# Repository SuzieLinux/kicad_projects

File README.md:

This repository has misc kicad projects
If you feel that it is worth something for you you can go to my website and make a donation using the donate button which brings you to paypal
https://suzielinux.com/

The project lcd_adapter is a board to adapt the 3.2 or 3.4 inch LCD designed
for the RPI so they can be used with other boards like my RL78 boards or
Linux boards like the beagle boards, youyeetoo, cubitruck, odroid or others.

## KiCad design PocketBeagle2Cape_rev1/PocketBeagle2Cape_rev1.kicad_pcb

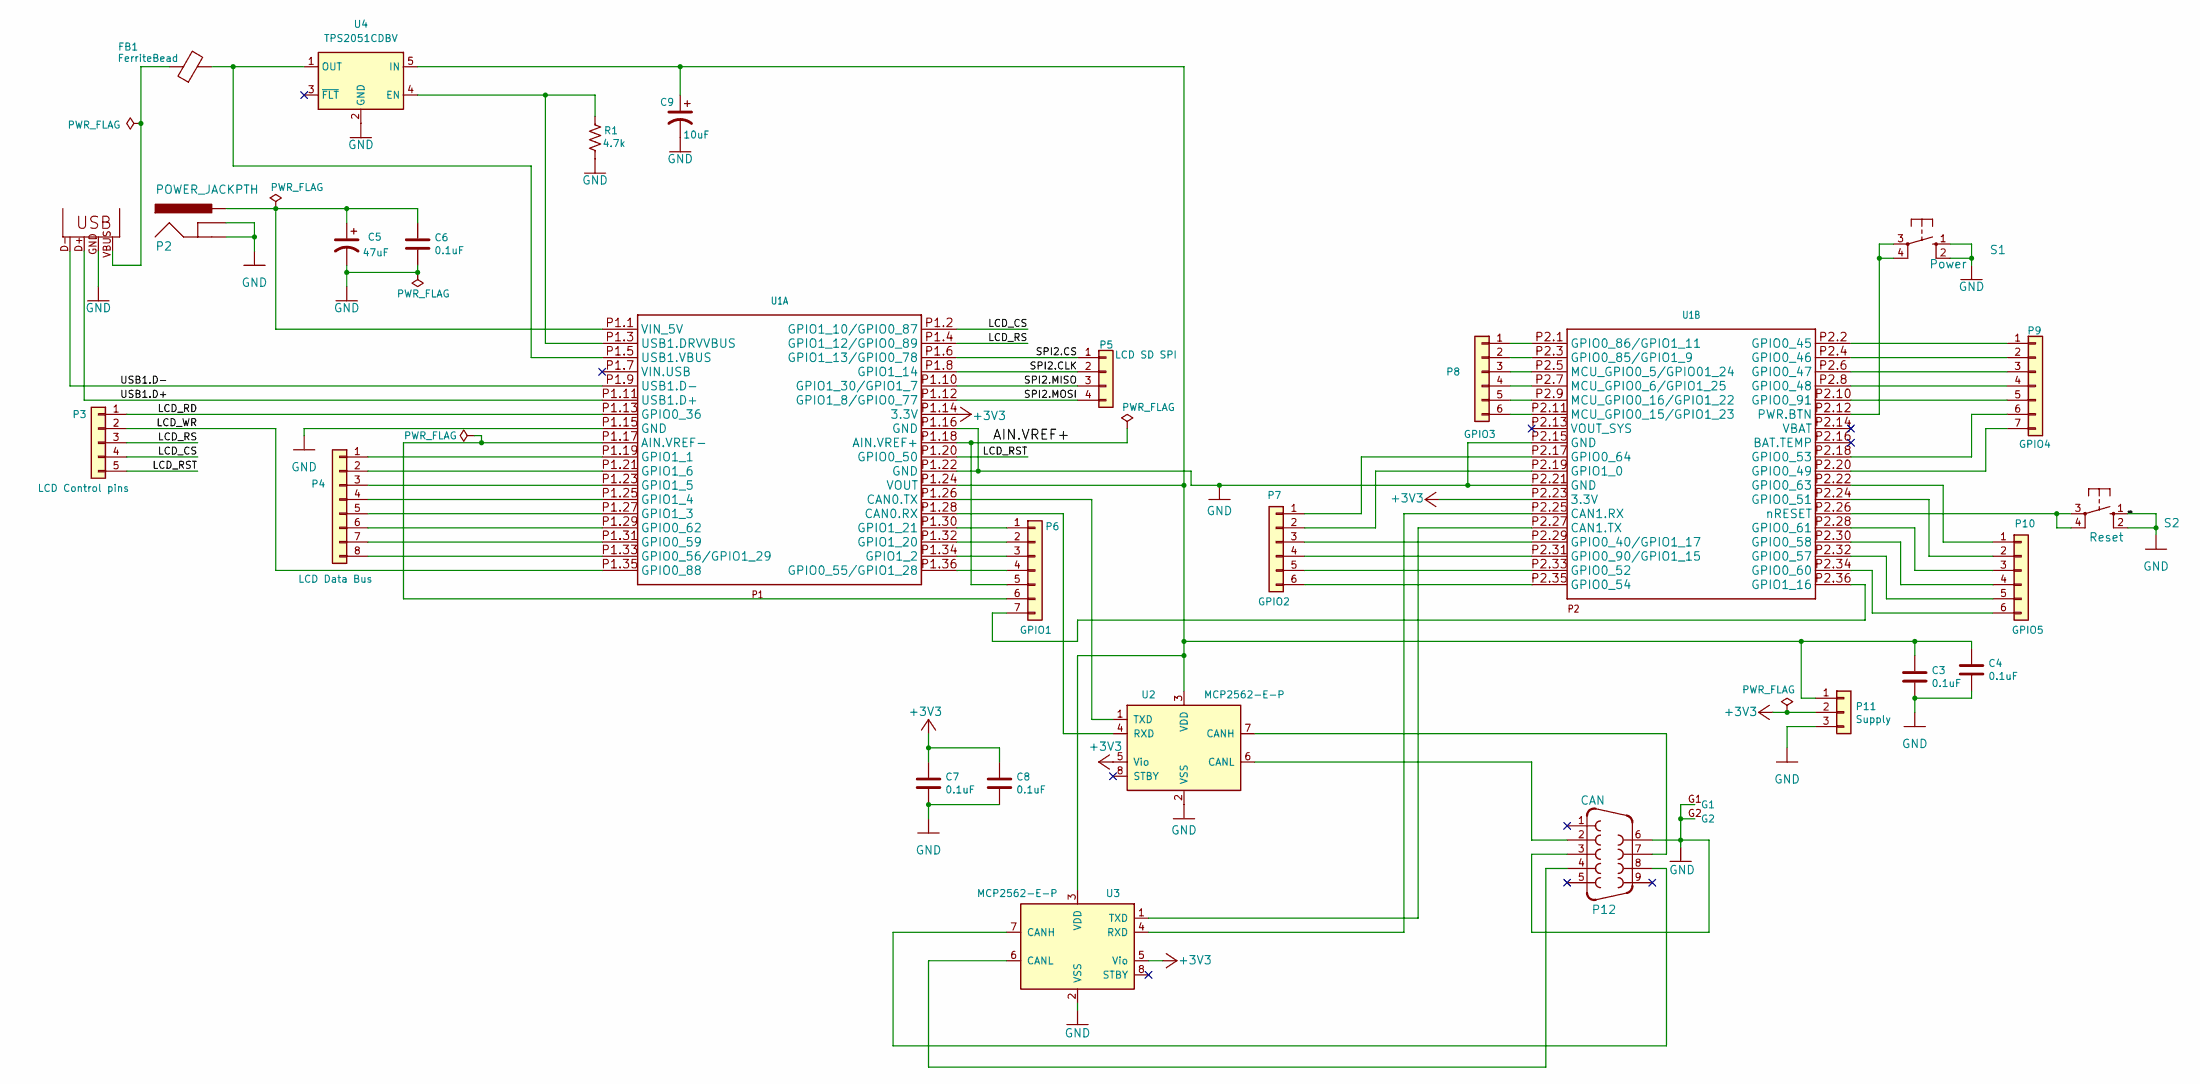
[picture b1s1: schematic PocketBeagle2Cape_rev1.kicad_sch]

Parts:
C3, C4, C6, C7, C8: 0.1uF; C_0805_2012Metric
C5: 47uF; CP_Radial_D6.3mm_P2.50mm
C9: 10uF; CP_Radial_D5.0mm_P2.50mm
FB1: FerriteBead; D_0805_2012Metric
P1: USB-A-H
P2: POWER_JACKPTH; POWER_JACK_PTH
P3: LCD Control pins; PinHeader_1x05_P2.00mm_Vertical
P4: LCD Data Bus; PinHeader_1x08_P2.00mm_Vertical
P5: LCD SD SPI; PinHeader_1x04_P2.00mm_Vertical
P6: GPIO1; PinHeader_1x07_P2.00mm_Vertical
P7: GPIO2; PinHeader_1x06_P2.00mm_Vertical
P8: GPIO3; PinHeader_1x06_P2.00mm_Vertical
P9: GPIO4; PinHeader_1x07_P2.00mm_Vertical
P10: GPIO5; PinHeader_1x06_P2.00mm_Vertical
P11: Supply; PinSocket_1x03_P2.54mm_Vertical
P12: CAN; F09HP
R1: 4.7k; R_0805_2012Metric
S1: Power; B3F-10XX
S2: Reset; B3F-10XX
U1: PocketBeagle2
U2, U3: MCP2562-E-P; SO-8_3.9x4.9mm_P1.27mm
U4: TPS2051CDBV; SOT-23-5

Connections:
+3V3: C7.1, C8.1, P11.2, U1.P1.14 (3.3V), U1.P2.23 (3.3V), U2.5 (Vio), U3.5 (Vio)
/AIN.VREF+: P6.5, U1.P1.18 (AIN.VREF+)
/LCD_CS: P3.4, U1.P1.2 (GPIO1_10/GPIO0_87)
/LCD_RD: P3.1, U1.P1.13 (GPIO0_36)
/LCD_RS: P3.3, U1.P1.4 (GPIO1_12/GPIO0_89)
/LCD_RST: P3.5, U1.P1.20 (GPIO0_50)
/LCD_WR: P3.2, U1.P1.35 (GPIO0_88)
/SPI2.CLK: P5.2, U1.P1.8 (GPIO1_14)
/SPI2.CS: P5.1, U1.P1.6 (GPIO1_13/GPIO0_78)
/SPI2.MISO: P5.3, U1.P1.10 (GPIO1_30/GPIO1_7)
/SPI2.MOSI: P5.4, U1.P1.12 (GPIO1_8/GPIO0_77)
/USB1.D+: P1.D+ (D-), U1.P1.11 (USB1.D+)
/USB1.D-: P1.D- (D+), U1.P1.9 (USB1.D-)
GND: C3.2, C4.2, C5.2, C6.2, C7.2, C8.2, C9.2, P1.GND (VBUS), P2.GND, P2.GNDBREAK, P11.3, P12.3, P12.6, P12.G1, P12.G2, R1.2, S1.1 (S), S1.2 (S1), S2.1 (S), S2.2 (S1), U1.P1.15 (GND), U1.P1.16 (GND), U1.P1.22 (GND), U1.P2.15 (GND), U1.P2.21 (GND), U2.2 (VSS), U3.2 (VSS), U4.2 (GND)
unnamed: FB1.1, P1.VBUS (GND)
unnamed: P4.1, U1.P1.19 (GPIO1_1)
unnamed: P4.2, U1.P1.21 (GPIO1_6)
unnamed: P4.3, U1.P1.23 (GPIO1_5)
unnamed: P4.4, U1.P1.25 (GPIO1_4)
unnamed: P4.5, U1.P1.27 (GPIO1_3)
unnamed: P4.6, U1.P1.29 (GPIO0_62)
unnamed: P4.7, U1.P1.31 (GPIO0_59)
unnamed: P4.8, U1.P1.33 (GPIO0_56/GPIO1_29)
unnamed: P6.1, U1.P1.30 (GPIO1_21)
unnamed: P6.2, U1.P1.32 (GPIO1_20)
unnamed: P6.3, U1.P1.34 (GPIO1_2)
unnamed: P6.4, U1.P1.36 (GPIO0_55/GPIO1_28)
unnamed: P6.6, U1.P1.17 (AIN.VREF-)
unnamed: P6.7, U1.P2.36 (GPIO1_16)
unnamed: P7.1, U1.P2.17 (GPIO0_64)
unnamed: P7.2, U1.P2.19 (GPIO1_0)
unnamed: P7.3, U1.P2.29 (GPIO0_40/GPIO1_17)
unnamed: P7.4, U1.P2.31 (GPIO0_90/GPIO1_15)
unnamed: P7.5, U1.P2.33 (GPIO0_52)
unnamed: P7.6, U1.P2.35 (GPIO0_54)
unnamed: P8.1, U1.P2.1 (GPIO0_86/GPIO1_11)
unnamed: P8.2, U1.P2.3 (GPIO0_85/GPIO1_9)
unnamed: P8.3, U1.P2.5 (MCU_GPIO0_5/GPIO01_24)
unnamed: P8.4, U1.P2.7 (MCU_GPIO0_6/GPIO1_25)
unnamed: P8.5, U1.P2.9 (MCU_GPIO0_16/GPIO1_22)
unnamed: P8.6, U1.P2.11 (MCU_GPIO0_15/GPIO1_23)
unnamed: P9.1, U1.P2.2 (GPIO0_45)
unnamed: P9.2, U1.P2.4 (GPIO0_46)
unnamed: P9.3, U1.P2.6 (GPIO0_47)
unnamed: P9.4, U1.P2.8 (GPIO0_48)
unnamed: P9.5, U1.P2.10 (GPIO0_91)
unnamed: P9.6, U1.P2.18 (GPIO0_53)
unnamed: P9.7, U1.P2.20 (GPIO0_49)
unnamed: P10.1, U1.P2.22 (GPIO0_63)
unnamed: P10.2, U1.P2.24 (GPIO0_51)
unnamed: P10.3, U1.P2.28 (GPIO0_61)
unnamed: P10.4, U1.P2.30 (GPIO0_58)
unnamed: P10.5, U1.P2.32 (GPIO0_57)
unnamed: P10.6, U1.P2.34 (GPIO0_60)
unnamed: C3.1, C4.1, C9.1, P11.1, U1.P1.24 (VOUT), U2.3 (VDD), U3.3 (VDD), U4.5 (IN)
unnamed: S1.3, S1.4 (P1), U1.P2.12 (PWR.BTN)
unnamed: S2.3, S2.4 (P1), U1.P2.26 (nRESET)
unnamed: U1.P1.28 (CAN0.RX), U2.4 (RXD)
unnamed: U1.P1.26 (CAN0.TX), U2.1 (TXD)
unnamed: R1.1, U1.P1.3 (USB1.DRVVBUS), U4.4 (EN)
unnamed: FB1.2, U1.P1.5 (USB1.VBUS), U4.1 (OUT)
unnamed: C5.1, C6.1, P2.PWR, U1.P1.1 (VIN_5V)
unnamed: U1.P2.25 (CAN1.RX), U3.4 (RXD)
unnamed: U1.P2.27 (CAN1.TX), U3.1 (TXD)
unnamed: P12.7, U2.7 (CANH)
unnamed: P12.2, U2.6 (CANL)
unnamed: P12.8, U3.7 (CANH)
unnamed: P12.4, U3.6 (CANL)

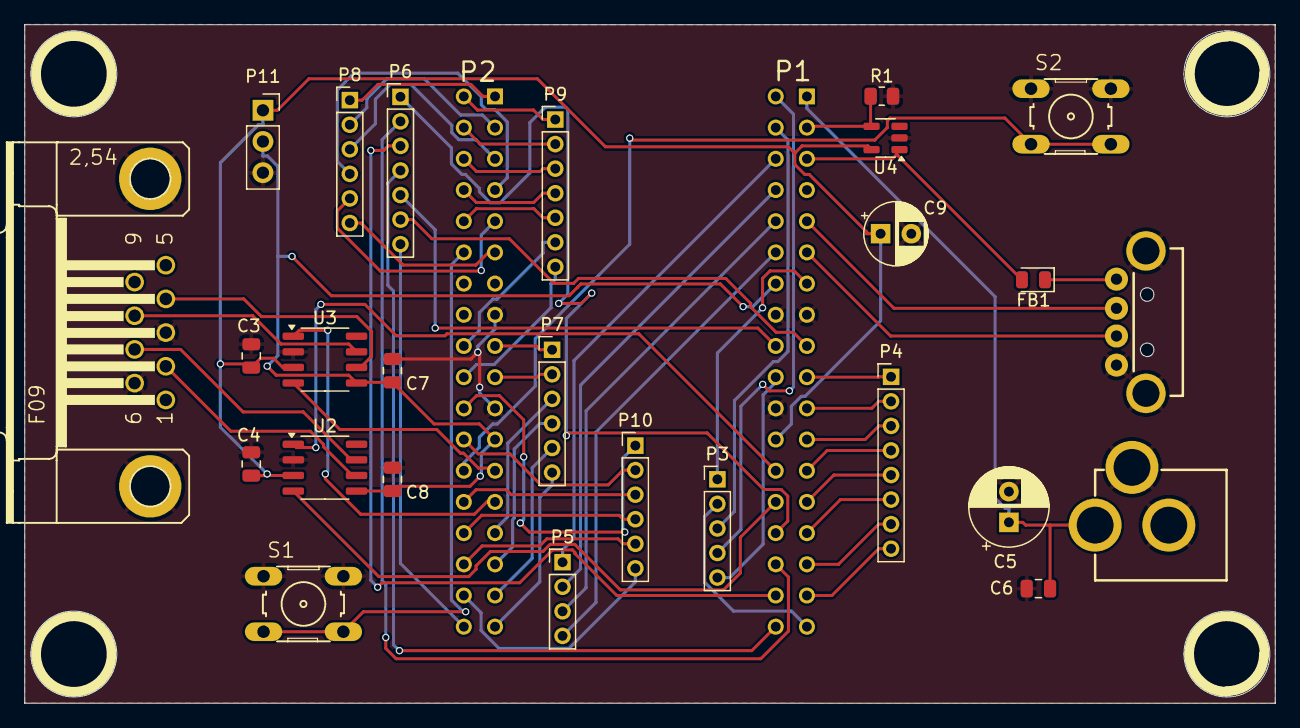
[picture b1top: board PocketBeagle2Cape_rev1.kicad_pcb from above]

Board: 2 copper layers, 101.8 x 55.2 mm, 27 parts (1 on the bottom side), 68 nets.

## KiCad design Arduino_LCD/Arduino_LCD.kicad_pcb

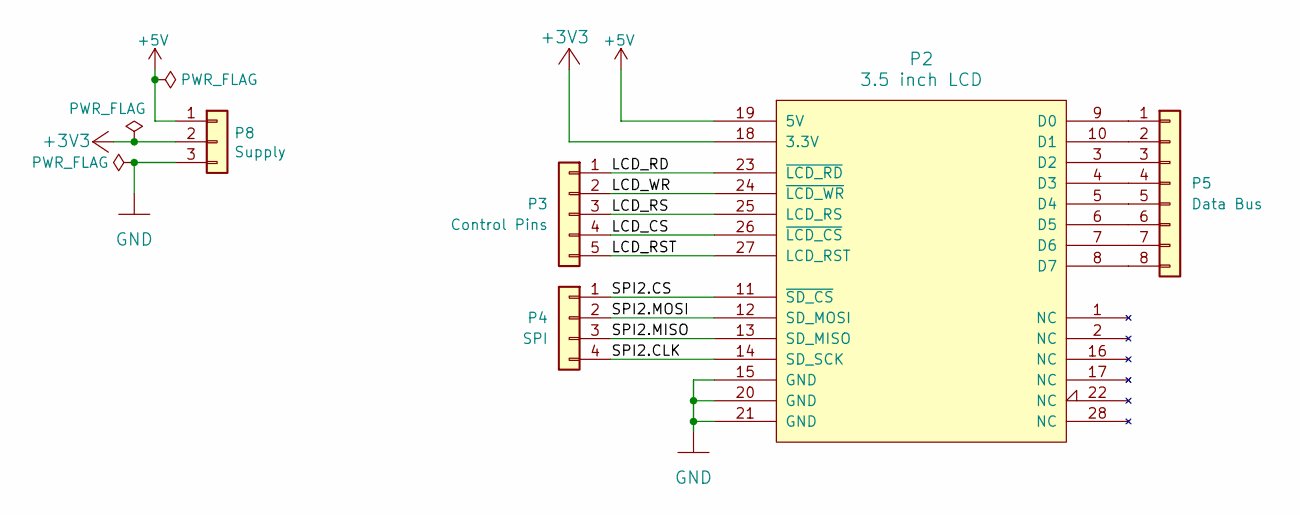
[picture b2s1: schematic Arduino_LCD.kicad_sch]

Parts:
P2: 3.5 inch LCD; ArduinoConnector
P3: Control Pins; PinHeader_1x05_P2.00mm_Vertical
P4: SPI; PinHeader_1x04_P2.00mm_Vertical
P5: Data Bus; PinHeader_1x08_P2.00mm_Vertical
P8: Supply; PinSocket_1x03_P2.54mm_Vertical

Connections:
+3V3: P2.18 (3.3V), P8.2
+5V: P2.19 (5V), P8.1
/LCD_CS: P2.26 (~LCD_CS), P3.4
/LCD_RD: P2.23 (~LCD_RD), P3.1
/LCD_RS: P2.25 (LCD_RS), P3.3
/LCD_RST: P2.27 (LCD_RST), P3.5
/LCD_WR: P2.24 (~LCD_WR), P3.2
/SPI2.CLK: P2.14 (SD_SCK), P4.4
/SPI2.CS: P2.11 (~SD_CS), P4.1
/SPI2.MISO: P2.13 (SD_MISO), P4.3
/SPI2.MOSI: P2.12 (SD_MOSI), P4.2
GND: P2.15 (GND), P2.20 (GND), P2.21 (GND), P8.3
unnamed: P2.9 (D0), P5.1
unnamed: P2.10 (D1), P5.2
unnamed: P2.3 (D2), P5.3
unnamed: P2.4 (D3), P5.4
unnamed: P2.5 (D4), P5.5
unnamed: P2.6 (D5), P5.6
unnamed: P2.7 (D6), P5.7
unnamed: P2.8 (D7), P5.8

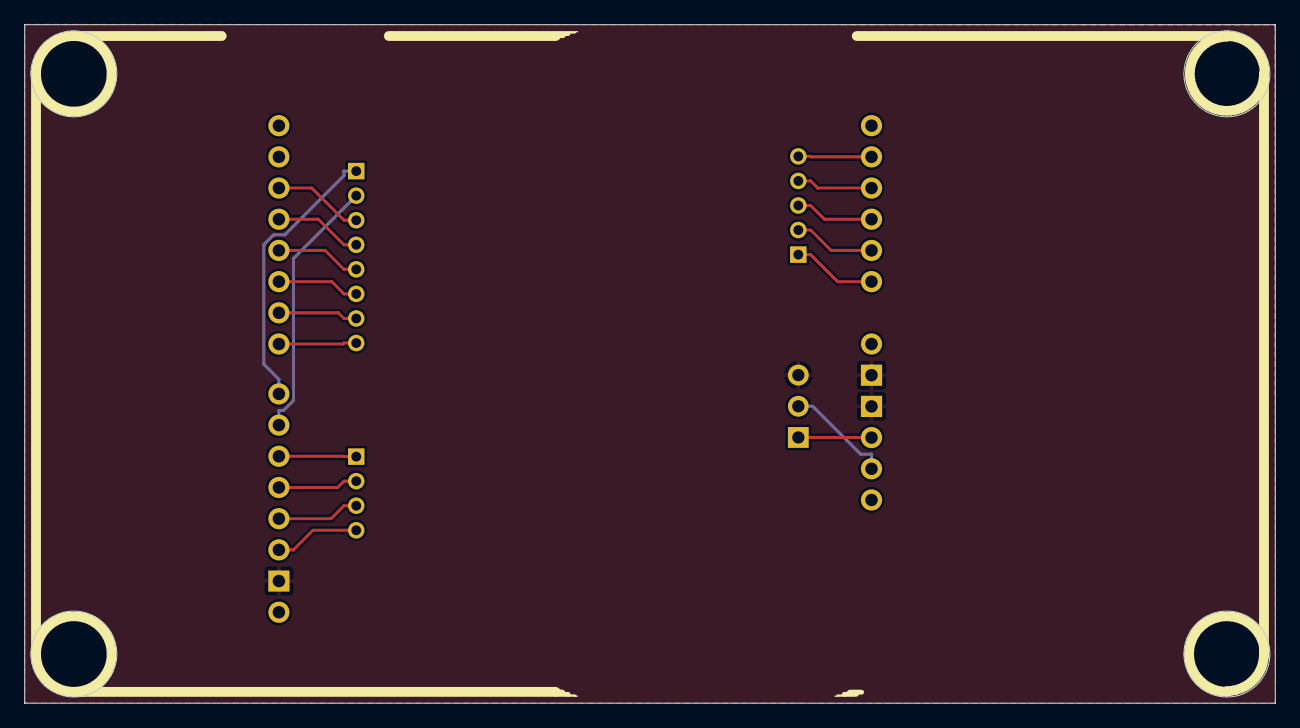
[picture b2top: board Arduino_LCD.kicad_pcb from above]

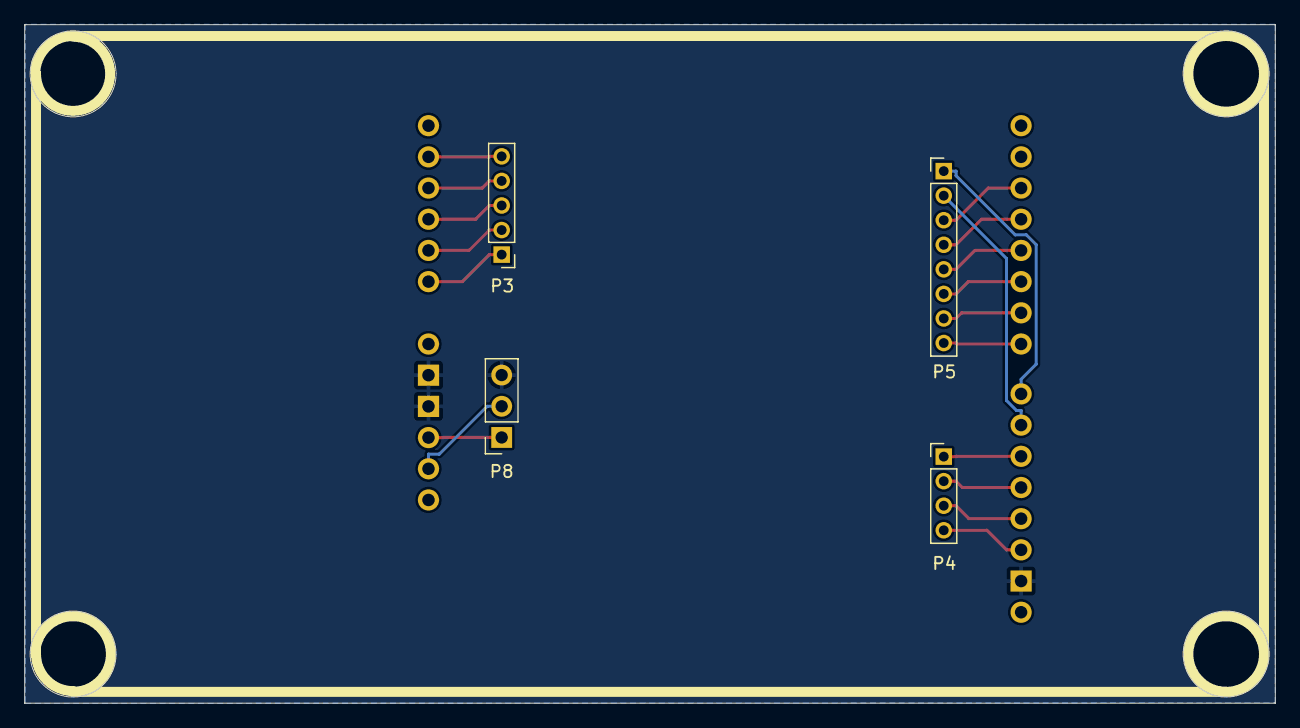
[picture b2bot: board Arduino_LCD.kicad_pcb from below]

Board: 2 copper layers, 101.8 x 55.2 mm, 5 parts (4 on the bottom side), 20 nets.

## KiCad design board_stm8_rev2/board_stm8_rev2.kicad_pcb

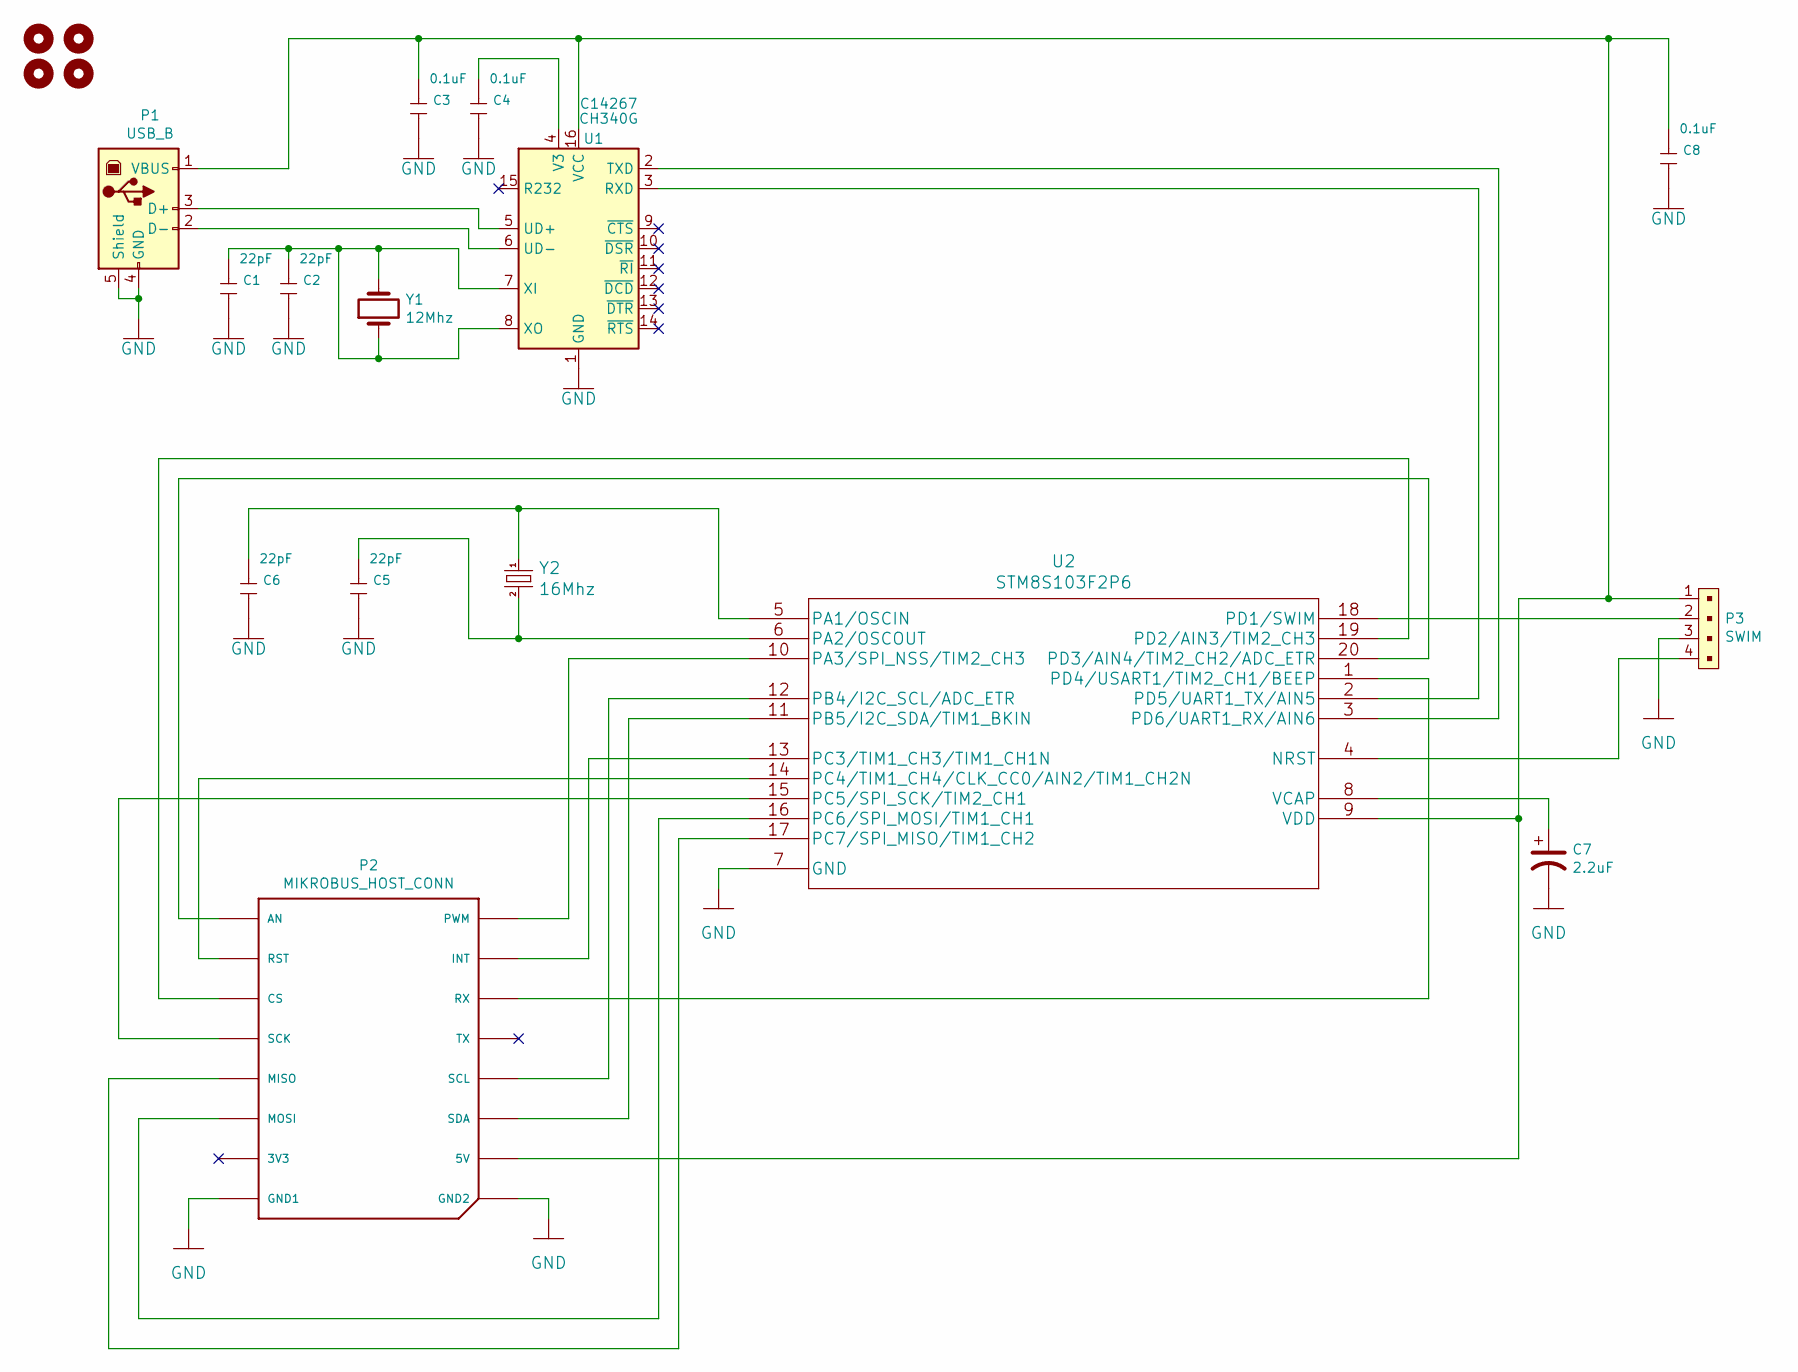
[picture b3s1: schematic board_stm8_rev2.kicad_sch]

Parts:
C1, C2, C5, C6: 22pF; C_0805_2012Metric_Pad1.18x1.45mm_HandSolder; MPN CC0603KRX7R9BB104; LCSC C1562
C3, C4, C8: 0.1uF; C_0805_2012Metric_Pad1.18x1.45mm_HandSolder; MPN CC0603KRX7R9BB104; LCSC C14663
C7: 2.2uF; C_Radial_D5.0mm_H5.0mm_P2.00mm
H1, H2, H3, H4: MountingHole; MountingHole_2.7mm_M2.5_DIN965_Pad
P1: USB_B; USB_B_Lumberg_2411_02_Horizontal
P2: MIKROBUS_HOST_CONN
P3: SWIM; PinHeader_1x4_P2.54mm_Drill1.02mm; MPN 0022232041; Digi-Key_PN WM4202-ND
U1: CH340G; SOIC-16_3.9x9.9mm_P1.27mm; LCSC C14267
U2: STM8S103F2P6
Y1: 12Mhz; Crystal_HC49-4H_Vertical
Y2: 16Mhz; Crystal_HC49-4H_Vertical

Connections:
GND: C1.2, C2.2, C3.2, C4.2, C5.2, C6.2, C7.2, C8.2, P1.4 (GND), P1.5 (Shield), P2.P8 (GND1), P2.P9 (GND2), P3.3, U1.1 (GND), U2.7 (GND)
unnamed: P1.3 (D+), U1.5 (UD+)
unnamed: P1.2 (D-), U1.6 (UD-)
unnamed: C3.1, C8.1, P1.1 (VBUS), P2.P10 (5V), P3.1, U1.16 (VCC), U2.9 (VDD)
unnamed: P2.P1 (AN), U2.20 (PD3/AIN4/TIM2_CH2/ADC_ETR)
unnamed: P2.P3 (CS), U2.19 (PD2/AIN3/TIM2_CH3)
unnamed: P2.P15 (INT), U2.13 (PC3/TIM1_CH3/TIM1_CH1N)
unnamed: P2.P5 (MISO), U2.17 (PC7/SPI_MISO/TIM1_CH2)
unnamed: P2.P6 (MOSI), U2.16 (PC6/SPI_MOSI/TIM1_CH1)
unnamed: P2.P16 (PWM), U2.10 (PA3/SPI_NSS/TIM2_CH3)
unnamed: P2.P2 (RST), U2.14 (PC4/TIM1_CH4/CLK_CC0/AIN2/TIM1_CH2N)
unnamed: P2.P14 (RX), U2.1 (PD4/USART1/TIM2_CH1/BEEP)
unnamed: P2.P4 (SCK), U2.15 (PC5/SPI_SCK/TIM2_CH1)
unnamed: P2.P12 (SCL), U2.12 (PB4/I2C_SCL/ADC_ETR)
unnamed: P2.P11 (SDA), U2.11 (PB5/I2C_SDA/TIM1_BKIN)
unnamed: U1.3 (RXD), U2.2 (PD5/UART1_TX/AIN5)
unnamed: U1.2 (TXD), U2.3 (PD6/UART1_RX/AIN6)
unnamed: C4.1, U1.4 (V3)
unnamed: C1.1, C2.1, U1.7 (XI), U1.8 (XO), Y1.1, Y1.2
unnamed: P3.4, U2.4 (NRST)
unnamed: C6.1, U2.5 (PA1/OSCIN), Y2.1
unnamed: C5.1, U2.6 (PA2/OSCOUT), Y2.2
unnamed: P3.2, U2.18 (PD1/SWIM)
unnamed: C7.1, U2.8 (VCAP)

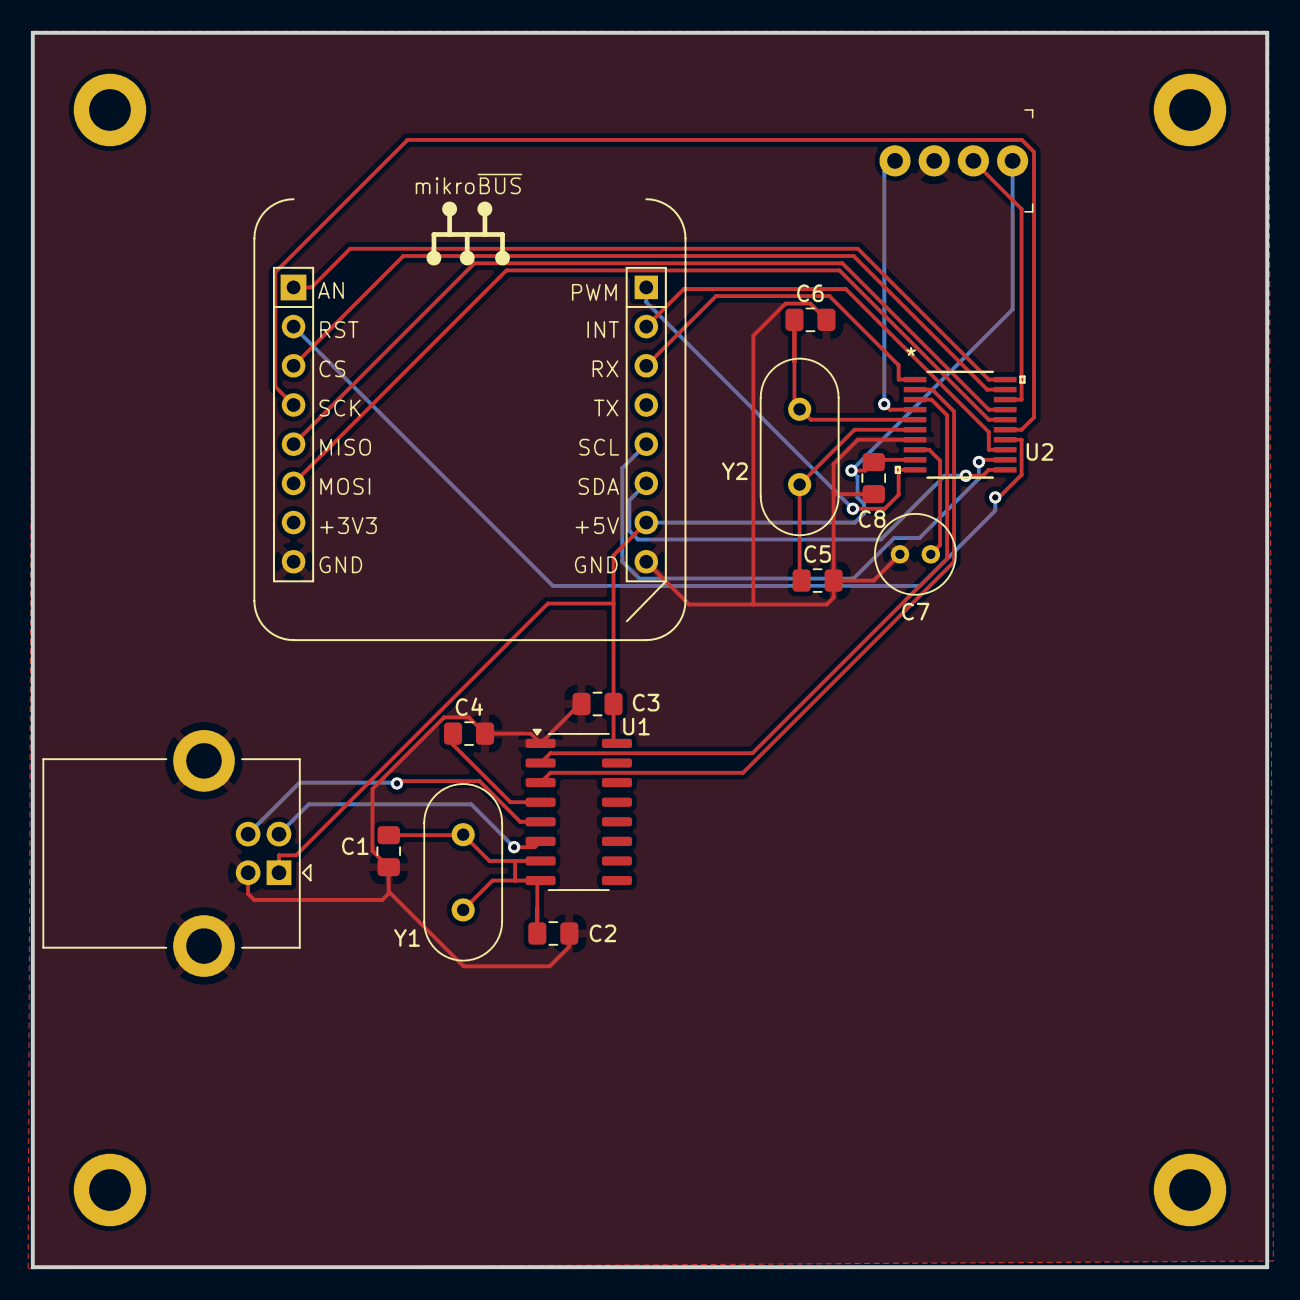
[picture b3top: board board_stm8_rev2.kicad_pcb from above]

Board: 2 copper layers, 80.0 x 80.0 mm, 19 parts (0 on the bottom side), 24 nets.

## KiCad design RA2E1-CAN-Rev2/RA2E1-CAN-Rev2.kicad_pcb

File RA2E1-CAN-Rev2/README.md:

This board uses Renesas R7FA2E1A93 Arm Cortex-M23 device

This is work in progress. I need to test with the evaluation board before I
finalize the design and order boards.

The LCD is Chanruida 1.8 inch TFT LCD 128 × 160 color screen 
ST7735 SPI display LCD module with SD card slot arduino display display lcd

The ethernet adapter is a small board called W5500 SPI to LAN ethernet
network module

It uses a MC2518FD CAN FD device

The debugger used is E2 Lite.

Feel free to use this board but if you are going to make money with it be
nice enough to make a donation on my website.

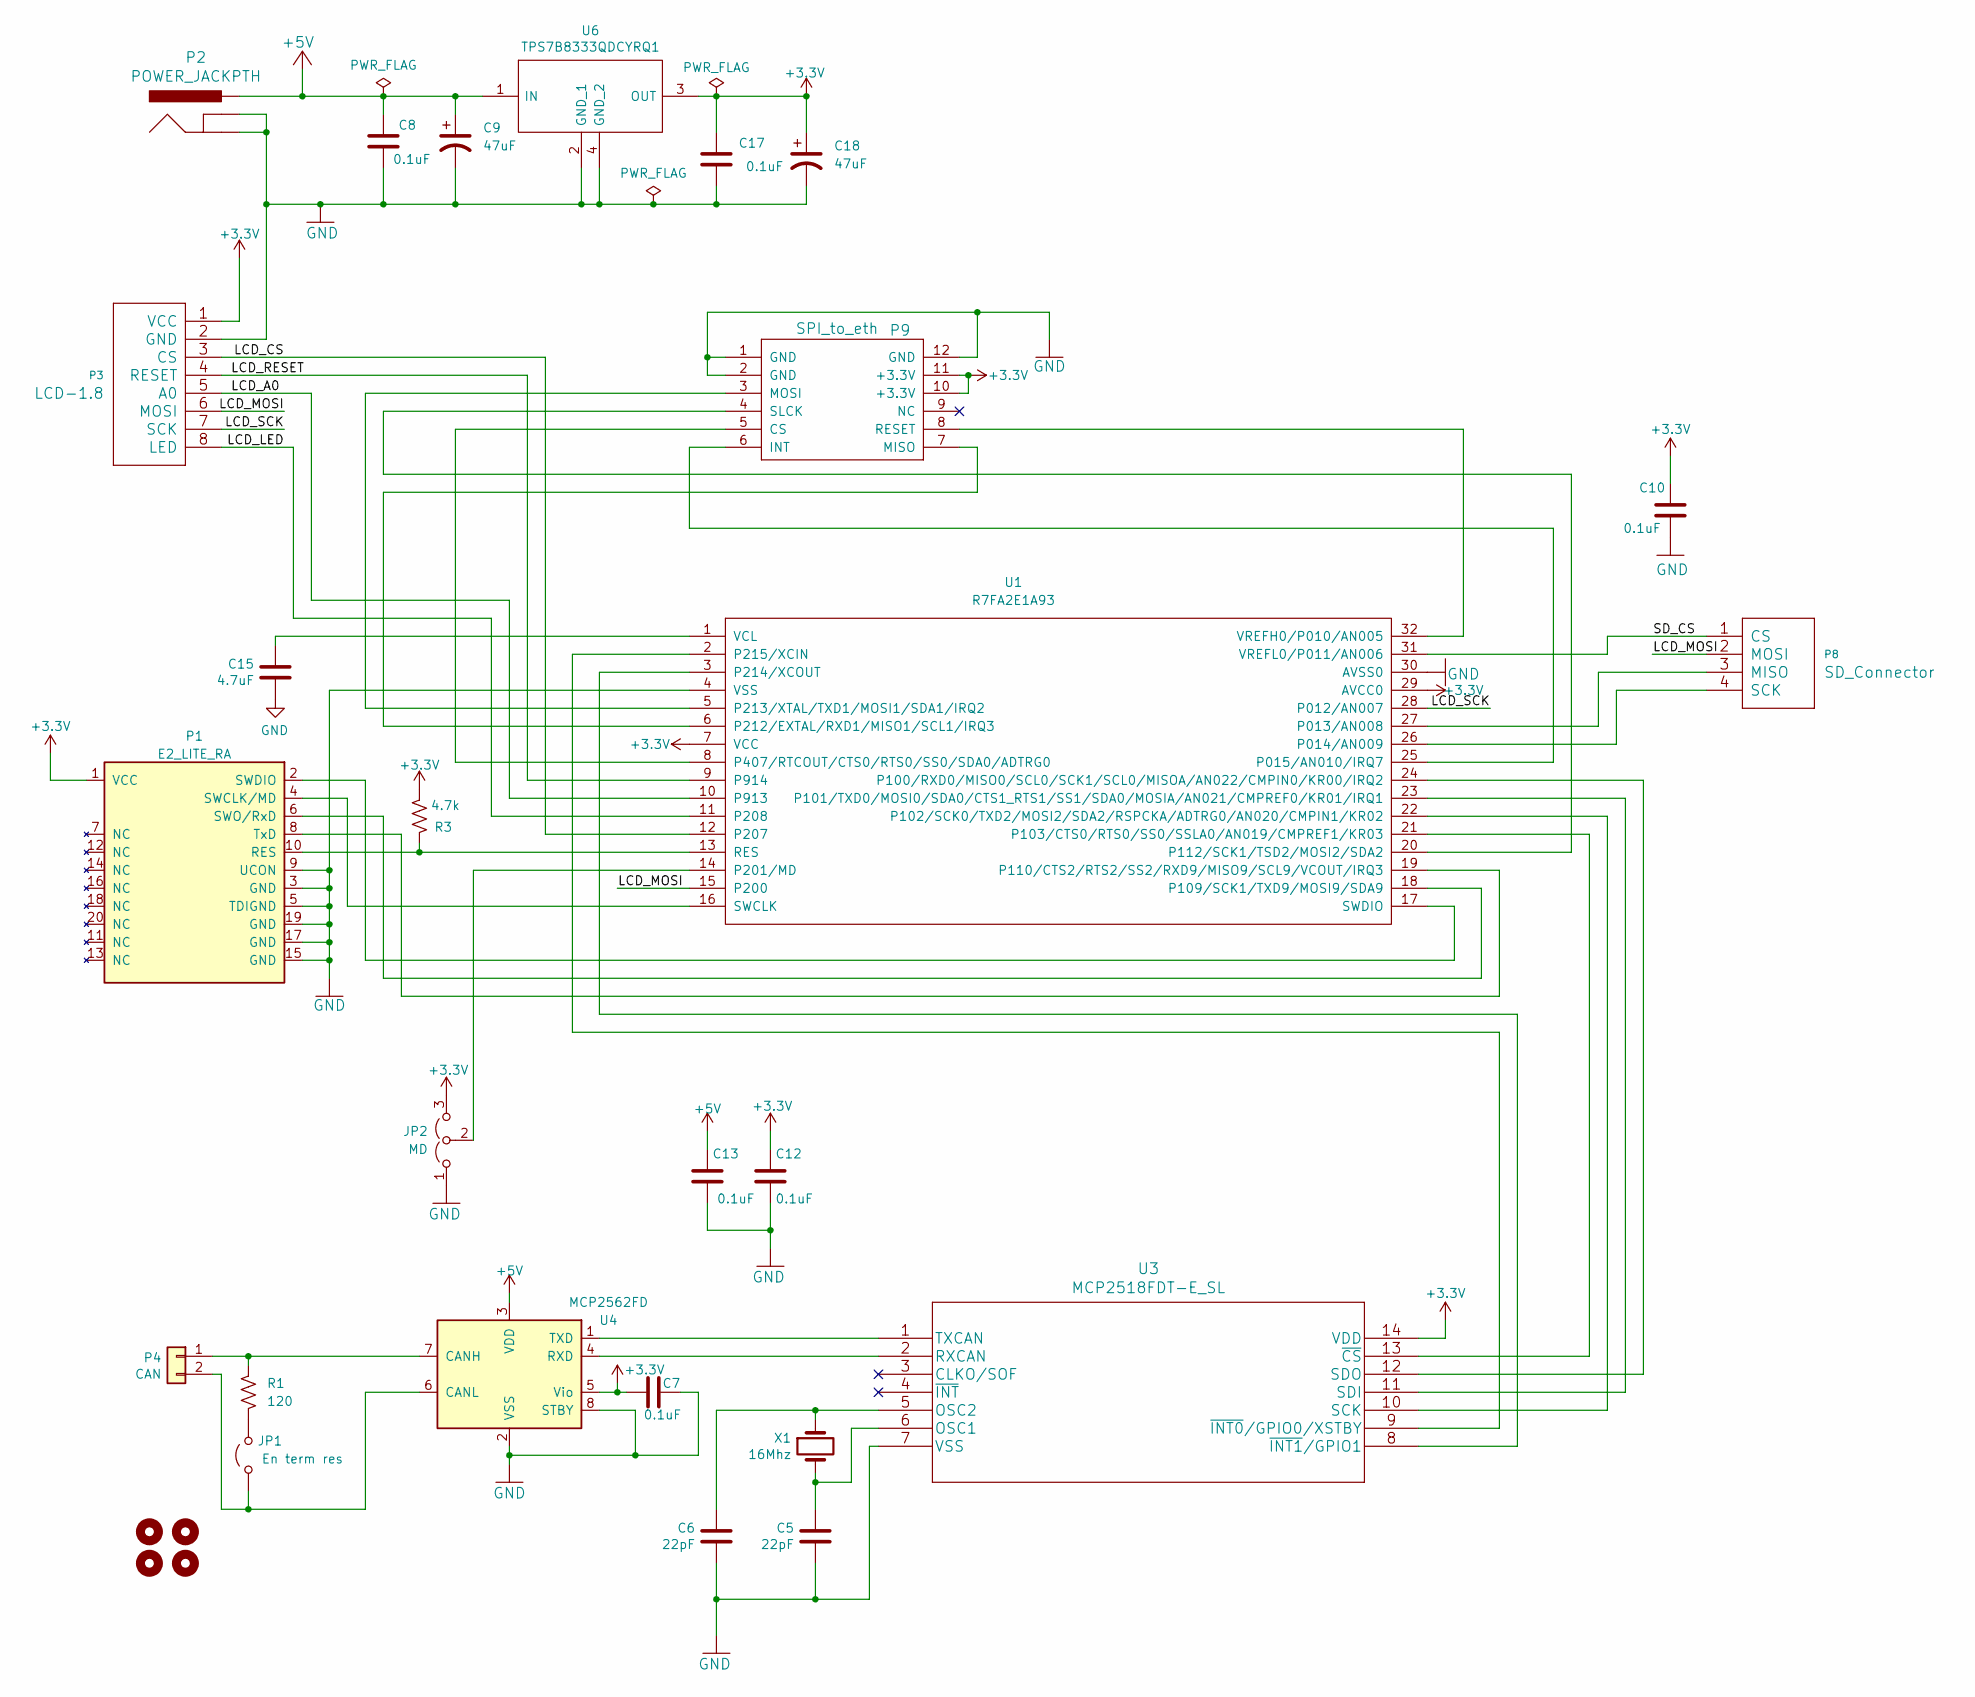
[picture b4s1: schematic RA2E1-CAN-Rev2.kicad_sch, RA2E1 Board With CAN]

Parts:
C5, C6: 22pF; C_0805_2012Metric_Pad1.18x1.45mm_HandSolder
C7, C8, C10, C12, C13, C17: 0.1uF; C_0805_2012Metric_Pad1.18x1.45mm_HandSolder
C9, C18: 47uF; CP_Radial_D6.3mm_P2.50mm
C15: 4.7uF; C_0805_2012Metric_Pad1.18x1.45mm_HandSolder
H1, H2, H3, H4: MountingHole; MountingHole_2.7mm_M2.5_DIN965_Pad
JP1: En term res; PinHeader_1x02_P2.54mm_Vertical
JP2: MD; PinSocket_1x03_P2.54mm_Vertical
P1: E2_LITE_RA; PinHeader_2x10_P1.27mm_Vertical_SMD
P2: POWER_JACKPTH; POWER_JACK_PTH
P3: LCD-1.8; PinHeader_1x08_P2.54mm_Vertical
P4: CAN; PinSocket_1x02_P2.54mm_Vertical
P8: SD_Connector; PinHeader_1x04_P2.54mm_Vertical
P9: SPI_to_eth
R1: 120; R_2512_6332Metric_Pad1.40x3.35mm_HandSolder
R3: 4.7k; R_0805_2012Metric_Pad1.20x1.40mm_HandSolder
U1: R7FA2E1A93; LQFP-32_7x7mm
U3: MCP2518FDT-E_SL; MCP2518FD
U4: MCP2562FD; DIP-8_W7.62mm
U6: TPS7B8333QDCYRQ1; SOT230P700X180-4N
X1: 16Mhz; Crystal_HC49-4H_Vertical

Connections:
+3.3V: C7.1, C10.1, C12.1, C17.1, C18.1, JP2.3 (B), P1.1 (VCC), P3.1 (VCC), P9.10 (+3.3V), P9.11 (+3.3V), R3.2, U1.7 (VCC), U1.29 (AVCC0), U3.14 (VDD), U4.5 (Vio), U6.3 (OUT)
+5V: C8.1, C9.1, C13.1, P2.PWR, U4.3 (VDD), U6.1 (IN)
/LCD_A0: P3.5 (A0), U1.10 (P913)
/LCD_CS: P3.3 (CS), U1.12 (P207)
/LCD_LED: P3.8 (LED), U1.11 (P208)
/LCD_MOSI: P3.6 (MOSI), P8.2 (MOSI), U1.15 (P200)
/LCD_RESET: P3.4 (RESET), U1.9 (P914)
/LCD_SCK: P3.7 (SCK), U1.28 (P012/AN007)
/SD_CS: P8.1 (CS), U1.31 (VREFL0/P011/AN006)
GND: C5.2, C6.2, C7.2, C8.2, C9.2, C10.2, C12.2, C13.2, C15.2, C17.2, C18.2, JP2.1 (A), P1.3 (GND), P1.5 (TDIGND), P1.9 (UCON), P1.15 (GND), P1.17 (GND), P1.19 (GND), P2.GND, P2.GNDBREAK, P3.2 (GND), P9.1 (GND), P9.2 (GND), P9.12 (GND), U1.4 (VSS), U1.30 (AVSS0), U3.7 (VSS), U4.2 (VSS), U4.8 (STBY), U6.2 (GND_1), U6.4 (GND_2)
unnamed: JP1.1 (A), P4.2, U4.6 (CANL)
unnamed: JP1.2 (B), R1.2
unnamed: JP2.2 (C), U1.14 (P201/MD)
unnamed: P1.10 (RES), R3.1, U1.13 (RES)
unnamed: P1.4 (SWCLK/MD), U1.16 (SWCLK)
unnamed: P1.2 (SWDIO), U1.17 (SWDIO)
unnamed: P1.6 (SWO/RxD), U1.18 (P109/SCK1/TXD9/MOSI9/SDA9)
unnamed: P1.8 (TxD), U1.19 (P110/CTS2/RTS2/SS2/RXD9/MISO9/SCL9/VCOU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)
unnamed: P4.1, R1.1, U4.7 (CANH)
unnamed: P8.3 (MISO), U1.27 (P013/AN008)
unnamed: P8.4 (SCK), U1.26 (P014/AN009)
unnamed: P9.5 (CS), U1.8 (P407/RTCOUT/CTS0/RTS0/SS0/SDA0/ADTRG0)
unnamed: P9.6 (INT), U1.25 (P015/AN010/IRQ7)
unnamed: P9.7 (MISO), U1.6 (P212/EXTAL/RXD1/MISO1/SCL1/IRQ3)
unnamed: P9.3 (MOSI), U1.5 (P213/XTAL/TXD1/MOSI1/SDA1/IRQ2)
unnamed: P9.8 (RESET), U1.32 (VREFH0/P010/AN005)
unnamed: P9.4 (SLCK), U1.20 (P112/SCK1/TSD2/MOSI2/SDA2)
unnamed: U1.24 (P100/RXD0/MISO0/SCL0/SCK1/SCL0/MISOA/AN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), U3.12 (SDO)
unnamed: U1.23 (P101/TXD0/MOSI0/SDA0/CTS1_RTS1/SS1/SDA0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), U3.11 (SDI)
unnamed: U1.22 (P102/SCK0/TXD2/MOSI2/SDA2/RSPCKA/ADTRG0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), U3.10 (SCK)
unnamed: U1.21 (P103/CTS0/RTS0/SS0/SSLA0/AN019/CMPREF1/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), U3.13 (~CS)
unnamed: U1.3 (P214/XCOUT), U3.8 (~INT1/GPIO1)
unnamed: U1.2 (P215/XCIN), U3.9 (~INT0/GPIO0/XSTBY)
unnamed: C15.1, U1.1 (VCL)
unnamed: C5.1, U3.6 (OSC1), X1.2
unnamed: C6.1, U3.5 (OSC2), X1.1
unnamed: U3.2 (RXCAN), U4.4 (RXD)
unnamed: U3.1 (TXCAN), U4.1 (TXD)

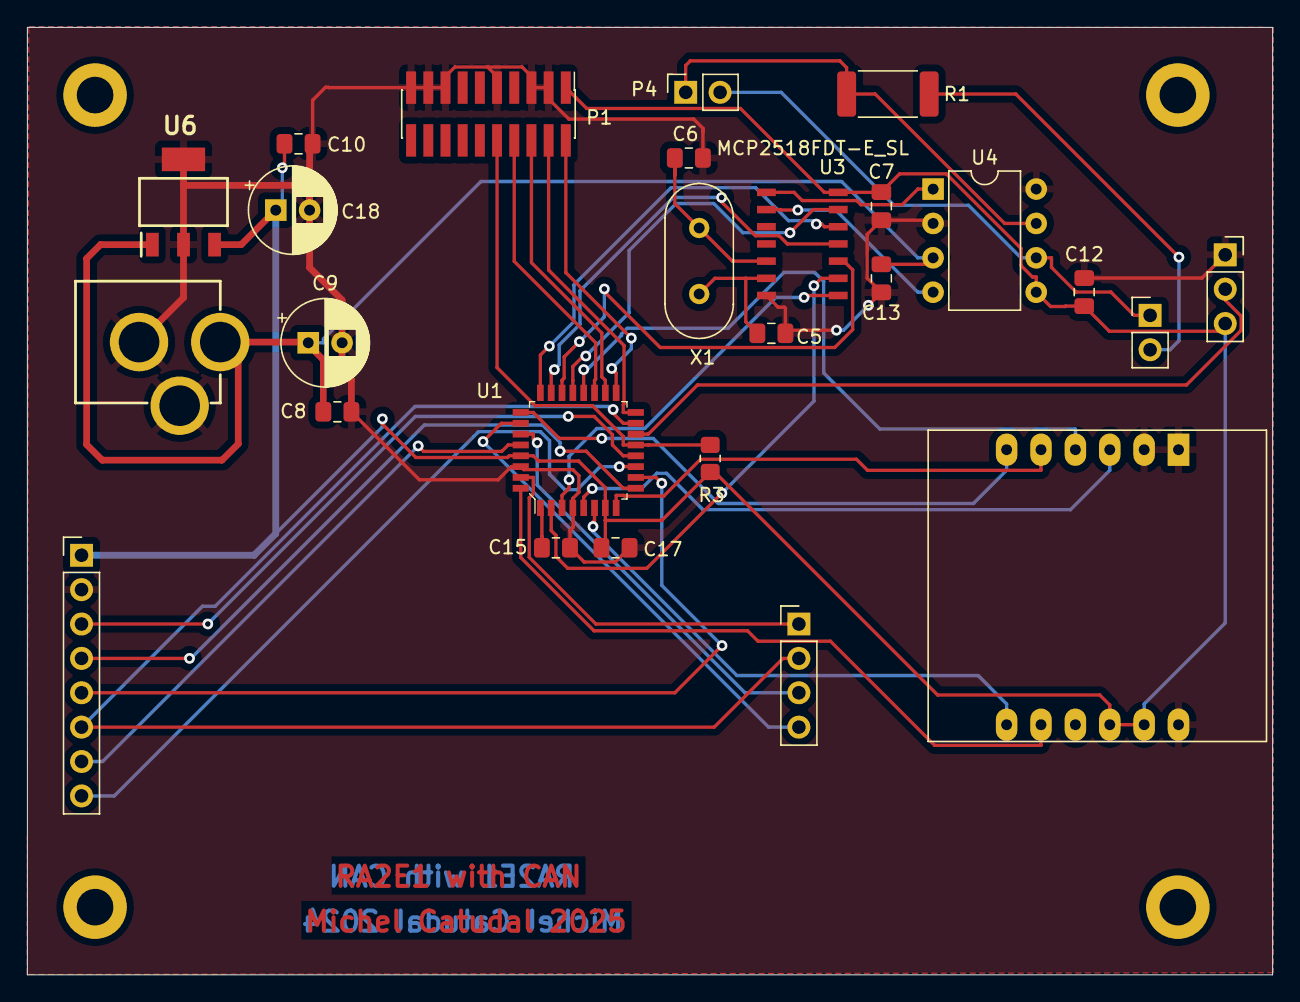
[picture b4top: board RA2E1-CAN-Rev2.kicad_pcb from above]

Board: 2 copper layers, 92.0 x 70.0 mm, 30 parts (0 on the bottom side), 38 nets.

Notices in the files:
parts and their libraries:
Copyright 2021 Accelerated Designs. All rights reserved.
Copyright 2016 Accelerated Designs. All rights reserved.
